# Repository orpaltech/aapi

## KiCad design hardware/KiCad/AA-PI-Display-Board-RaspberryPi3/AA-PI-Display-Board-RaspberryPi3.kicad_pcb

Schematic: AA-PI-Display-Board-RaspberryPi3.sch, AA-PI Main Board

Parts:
C1: 1u; C_0805_2012Metric_Pad1.15x1.40mm_HandSolder
C2, C9, C14, C15, C21, C26: 100n; C_0805_2012Metric_Pad1.15x1.40mm_HandSolder
C3, C7, C13: 4.7u; C_1206_3216Metric_Pad1.42x1.75mm_HandSolder
C4, C18: 10u; C_0805_2012Metric_Pad1.15x1.40mm_HandSolder
C5: 22u; C_1206_3216Metric_Pad1.42x1.75mm_HandSolder
C6: 10u; CP_EIA-3528-21_Kemet-B
C8: 47u; CP_EIA-3528-21_Kemet-B
C10, C27: 10u; C_1206_3216Metric_Pad1.42x1.75mm_HandSolder
C11, C12, C19: 10u; CP_EIA-3216-18_Kemet-A
C16, C17: 10n; C_0805_2012Metric_Pad1.15x1.40mm_HandSolder
C20: 2.2u; C_1206_3216Metric_Pad1.42x1.75mm_HandSolder
C22, C23: 22p; C_0805_2012Metric_Pad1.15x1.40mm_HandSolder
C24: 470u; CP_EIA-7343-31_Kemet-D
C25: 1u (>30V); C_1206_3216Metric_Pad1.42x1.75mm_HandSolder
D1: 1N4148; D_SOD-323_HandSoldering
D2, D3, D4, D7: B330B; D_SMB
D5: PESD5V0S1BA; D_SOD-323_HandSoldering
D6: Wall adapter; LED_0805_2012Metric_Pad1.15x1.40mm_HandSolder
D8: SS14; D_SMA
F1, F2: 2A 6V; Fuse_1206_3216Metric_Pad1.42x1.75mm_HandSolder
J1: CTP Interface; FPC-0.5-1-6P_Clamshell_Bottom
J2: USB_B_Micro; USB_Micro_B_Female_10118192
J3: USB_B_Mini; USB_Mini-B_Lumberg_2486_01_Horizontal
J4: Wall adapter; DC-050-SMD-Power-Jack
J5: MCU Power; JST_PH_B2B-PH-SM4-TB_1x02-1MP_P2.00mm_Vertical
J6: LCD Interface; FH26W-33S-0.3SHW; Manufacturer_Part_Number FH26-33S-0.3SHW
J7: Power Status; 1.25-AB-SMT-6pin-Vertical
J8: RaspberryPi MIPI-DSI Interface; FPC-1.0D-WTS-15P
J9: VNA Board Interface; 1.25-AB-SMT-10pin-Vertical
J10: MCU Interface; 1.25-AB-SMT-12pin-Vertical
J11: NTC Thermistor; JST_PH_B2B-PH-SM4-TB_1x02-1MP_P2.00mm_Vertical
J12: Battery; JST_PH_B2B-PH-SM4-TB_1x02-1MP_P2.00mm_Vertical
L1: 6.8uH; CDRH124
L2, L3: 0.5; L_0805_2012Metric_Pad1.15x1.40mm_HandSolder
L4: 10uH; CD54
Q1, Q3, Q7: IRLML6244; SOT-23
Q2, Q4, Q5, Q6, Q8: IRLML2244; SOT-23
R1, R4, R5, R9, R11, R16, R17, R20, R21, R28: 10K; R_0805_2012Metric_Pad1.15x1.40mm_HandSolder
R2, R6: 100K; R_0805_2012Metric_Pad1.15x1.40mm_HandSolder
R3: 0.5; R_0805_2012Metric_Pad1.15x1.40mm_HandSolder
R7: 300K; R_0805_2012Metric_Pad1.15x1.40mm_HandSolder
R8: 470K; R_0805_2012Metric_Pad1.15x1.40mm_HandSolder
R10: 330; R_0805_2012Metric_Pad1.15x1.40mm_HandSolder
R12, R13: 910; R_0805_2012Metric_Pad1.15x1.40mm_HandSolder
R14, R15: -; R_0805_2012Metric_Pad1.15x1.40mm_HandSolder
R18: 1.6M; R_0805_2012Metric_Pad1.15x1.40mm_HandSolder
R19: 390K; R_0805_2012Metric_Pad1.15x1.40mm_HandSolder
R22: 75K; R_0805_2012Metric_Pad1.15x1.40mm_HandSolder
R23: 2.2M; R_0805_2012Metric_Pad1.15x1.40mm_HandSolder
R24: 1K; R_0805_2012Metric_Pad1.15x1.40mm_HandSolder
R25, R26: 0; R_0805_2012Metric_Pad1.15x1.40mm_HandSolder
R27: 240K; R_0805_2012Metric_Pad1.15x1.40mm_HandSolder
R29: 33K; R_0805_2012Metric_Pad1.15x1.40mm_HandSolder
R30: 15; R_0805_2012Metric_Pad1.15x1.40mm_HandSolder
SW1: SW_SPST; SW_SPST_CK_RS282G05A3
SW2: SW_SPDT; SW_SPDT_PCM12
U1: LTC4412; SOT95P280X100-6N; Manufacturer_Part_Number LTC4412ES6#TRMPBF
U2: AMS1117-3.3; SOT-223-3_TabPin2; Manufacturer_Part_Number AMS1117-3.3
U3: WM8731; SOP65P780X200-28N; Manufacturer_Part_Number WM8731/L
U4: MCP73833; SOP50P490X110-10N; Manufacturer_Part_Number MCP73833-FCI/UN
U5: TPS61030PWP; SOP65P640X120-17N; Manufacturer_Part_Number TPS61030PWP
U6: FAN5333BSX; SOT95P270X145-5N; Manufacturer_Part_Number FAN5333BSX
Y1: 12.288M; Crystal_SMD_5032-2Pin_5.0x3.2mm

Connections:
+3V3: C8.1, C9.1, J1.1, J6.4, J6.27, J6.28, L2.1, L3.1, Q3.1, Q7.1, R4.2, R5.2, R9.2, R11.1, R16.1, R17.2, R29.2, U2.2
+5V: C6.1, C18.1, C20.1, C24.1, J5.1, J9.1, L4.1, R23.2, U2.3, U5.13, U5.14, U5.15, U6.5
/V_F2: D2.1, D3.1, D4.1, F2.1
/V_SUPPLY: C5.1, D5.2, F1.2, Q5.3
/V_USB: C3.1, F2.2, Q4.3, U1.1
/V_USB1: D2.2, J2.1
/V_USB2: D3.2, J3.1 (VBUS)
/V_WALL: F1.1, J4.1
CHRG_PG: J7.2, Q7.2, R17.1
CHRG_STAT1: J7.3, R16.2, U4.3
CHRG_STAT2: J7.4, R11.2, U4.4
CTP_INT: J1.3, J10.5
DSI_CLK_N: J6.15, J8.5
DSI_CLK_P: J6.16, J8.6
DSI_D0_N: J6.12, J8.8
DSI_D0_P: J6.13, J8.9
DSI_D1_N: J6.18, J8.2
DSI_D1_P: J6.19, J8.3
GND: C3.2, C6.2, C7.2, C8.2, C9.2, C10.2, C11.2, C12.2, C13.1, C14.2, C15.1, C16.2, C17.2, C18.2, C19.2, C20.2, C21.2, C22.2, C23.2, C24.2, C25.2, C26.2, C27.2, D4.2, D5.1, J1.6, J1.SH, J2.5, J2.SH, J3.5 (GND), J3.SH (Shield), J4.2, J4.3, J5.2, J6.1, J6.7, J6.8, J6.11, J6.14, J6.17, J6.20, J6.23, J6.26, J6.33, J6.SH1, J6.SH2, J7.6, J7.SH, J8.1, J8.4, J8.7, J8.10, J8.13, J8.SH, J9.2, J9.10, J9.SH, J10.6, J10.12, J10.SH, J11.2, J12.2, Q1.2, R3.1, R10.1, R14.1, R15.1, R19.1, R20.1, R22.2, R25.1, R27.2, R28.1, R30.2, SW1.1, U1.2, U1.3, U2.1, U3.15, U3.21, U3.22, U3.28, U4.5, U5.3, U5.4, U5.5, U5.8, U5.11, U5.17, U6.2
I2C_SCL: J1.5, J9.4, J10.2, R5.1, U3.24
I2C_SDA: J1.4, J9.3, J10.1, R4.1, U3.23
I2S_BCLK: J10.9, U3.3
I2S_DIN: J10.11, U3.6
I2S_LRCK: J10.10, U3.7
LCD_RESET: J1.2, J6.24, J10.4
LED-A: C25.1, D8.1, J6.31, J6.32
LED-K: J6.29, J6.30, R30.1, U6.3
LOW_BATT: J7.5, R29.1, U5.10
unnamed: C1.1, D1.1, R1.2, SW1.2
unnamed: C1.2, C2.2, Q1.3, Q2.1, R2.2
unnamed: C4.2, Q1.1, R7.2
unnamed: C5.2, R3.2
unnamed: C11.1, C14.1, L2.2, U3.14
unnamed: C12.1, C15.2, U3.16
unnamed: C16.1, R12.2, R14.2, U3.20
unnamed: C17.1, R13.2, R15.2, U3.19
unnamed: C19.1, C21.1, C26.1, L3.2, U3.1, U3.27
unnamed: C22.1, U3.26, Y1.2
unnamed: C23.1, U3.25, Y1.1
unnamed: C27.1, J12.1, Q8.3, U4.9, U4.10
unnamed: D1.2, Q3.3, R6.2, R7.1
unnamed: D6.1, R10.2
unnamed: D6.2, Q6.3
unnamed: D8.2, L4.2, U6.1
unnamed: J11.1, R26.2, R28.2
unnamed: L1.2, U5.1, U5.2
unnamed: Q4.1, U1.5
unnamed: Q5.1, Q6.1, R8.1, U1.4
unnamed: Q7.3, R21.2, U4.7
unnamed: R18.1, R19.2, U5.7
unnamed: R22.1, SW2.2, U6.4
unnamed: R23.1, R27.1, U5.12
unnamed: R24.1, R25.2
unnamed: R24.2, U4.6
unnamed: R26.1, U4.8
OUT_VI: J9.9, R13.1
OUT_VV: J9.8, R12.1
PWM_CABC: J6.25, SW2.1
PWM_MCU: J10.3, SW2.3
SHDN_CTRL: J7.1, Q3.2, R9.1
TE_OUT: J6.5
V_IN: C7.1, C13.2, D7.2, Q4.2, Q5.2, Q6.2, Q8.1, R8.2, R20.2, R21.1, U1.6, U4.1, U4.2
V_LOAD: C4.1, C10.1, L1.1, Q2.3, R6.1, R18.2, U5.6, U5.9
V_SW: C2.1, D7.1, Q2.2, Q8.2, R1.1, R2.1

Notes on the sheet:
The STAT pin goes low when the wall adapter is connected to the load.

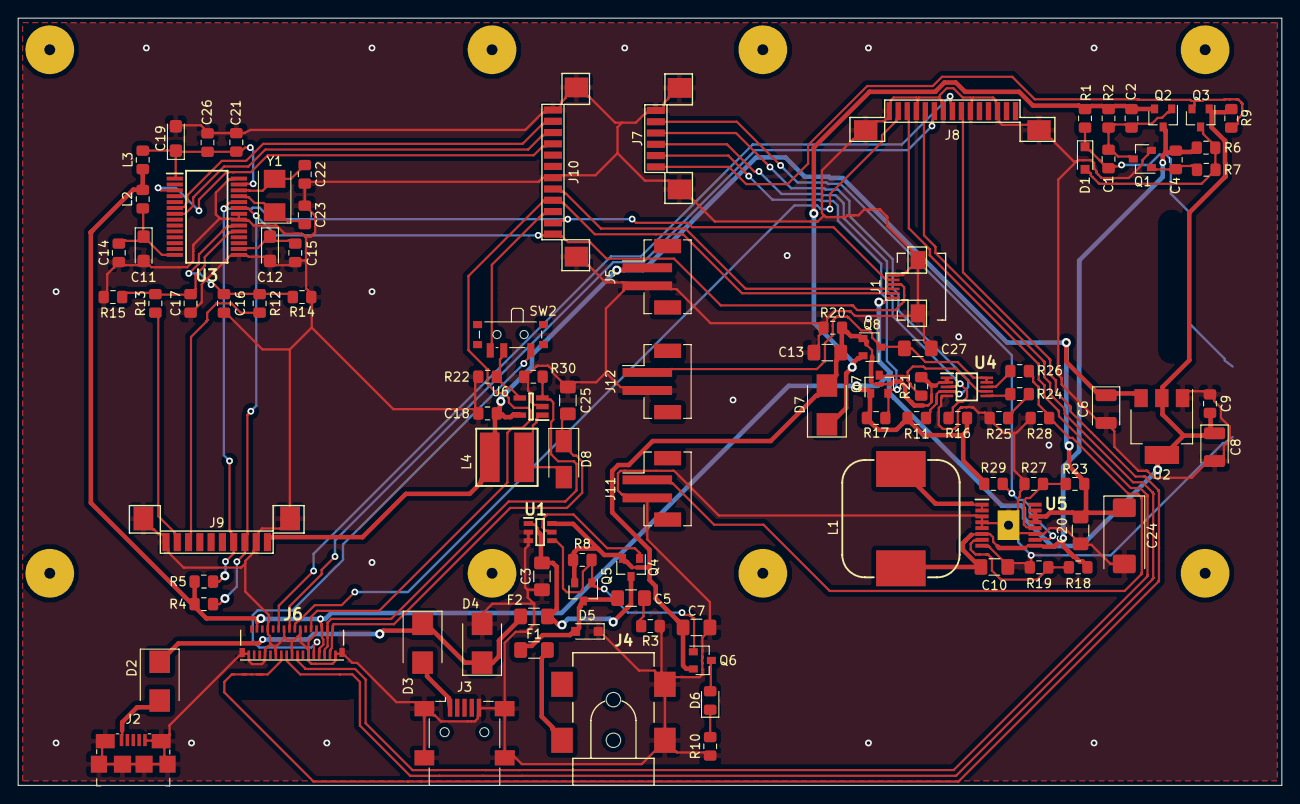
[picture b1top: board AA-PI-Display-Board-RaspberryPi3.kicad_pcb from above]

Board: 2 copper layers, 140.0 x 85.0 mm, 110 parts (1 on the bottom side), 63 nets.

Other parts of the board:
CH1: CTP-CABLE-HOLE
HOLE2: LCD-0.3-33P-CABLE-HOLE
SS1, SS2, SS3, SS4, SS5, SS6, SS7, SS8: PCB-Standoff-Spacer-SMD-M3

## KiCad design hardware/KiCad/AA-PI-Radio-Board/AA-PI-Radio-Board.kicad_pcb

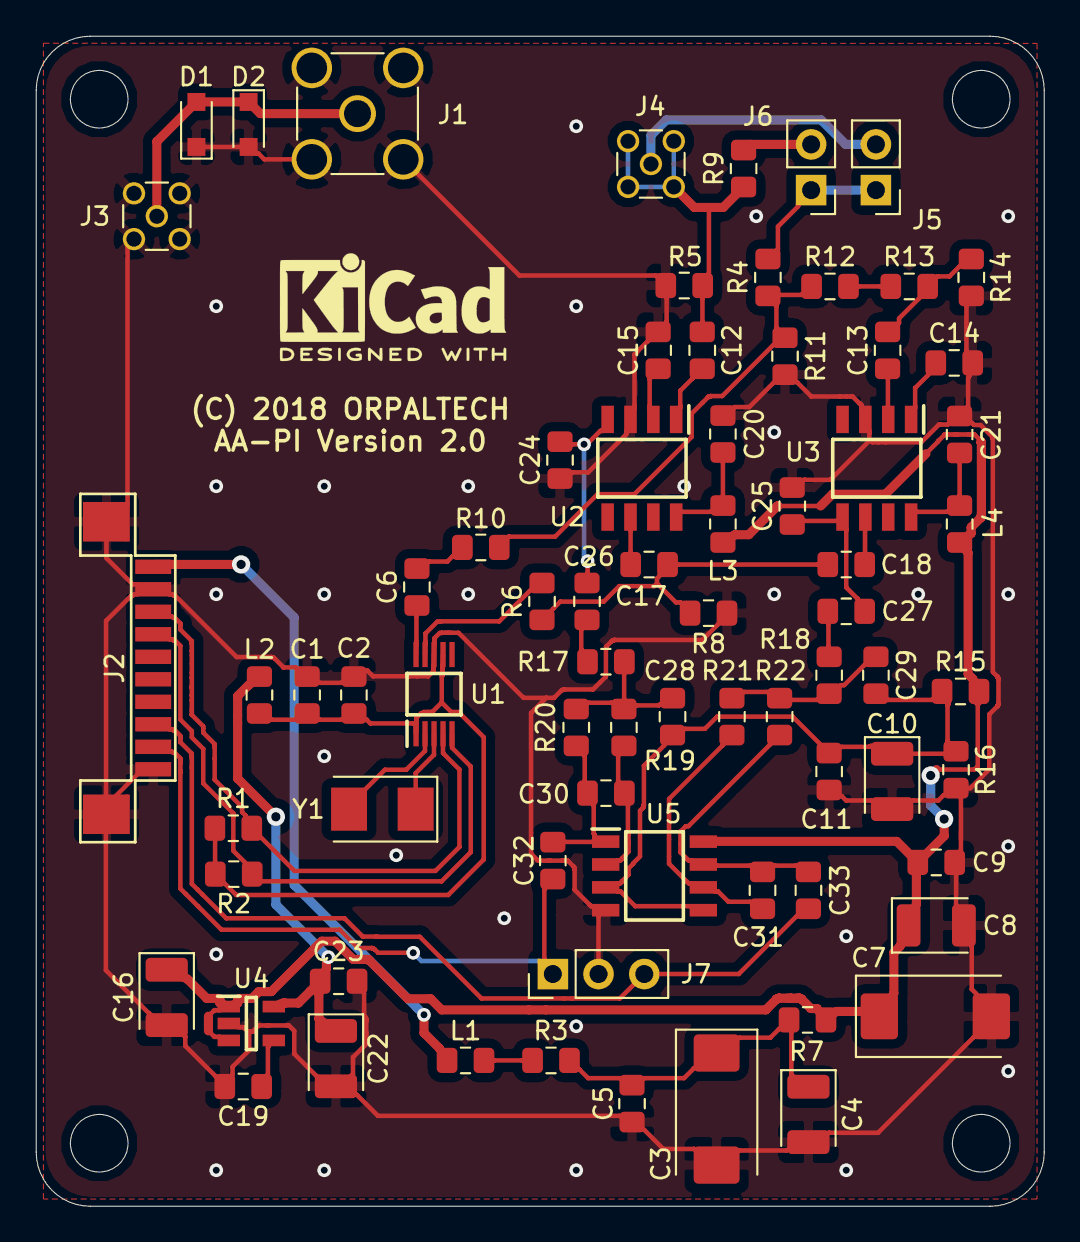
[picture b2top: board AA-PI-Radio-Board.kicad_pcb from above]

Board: 2 copper layers, 56.0 x 65.0 mm, 78 parts (0 on the bottom side), 45 nets.

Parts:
C1: 100p; C_0805_2012Metric_Pad1.15x1.40mm_HandSolder
C2, C5, C6, C9, C11, C12, C13, C14, C15, C20, C21, C23, C26, C27: 100n; C_0805_2012Metric_Pad1.15x1.40mm_HandSolder
C3, C7: 100u; CP_EIA-7343-31_Kemet-D
C4: 47u; CP_EIA-3528-21_Kemet-B
C8: 22u; CP_EIA-3528-21_Kemet-B
C10, C16, C22: 10u; CP_EIA-3528-21_Kemet-B
C17, C18: 10n; C_0805_2012Metric_Pad1.15x1.40mm_HandSolder
C19: 22n; C_0805_2012Metric_Pad1.15x1.40mm_HandSolder
C24, C25: 300p; C_0805_2012Metric_Pad1.15x1.40mm_HandSolder
C28, C29: 1n; C_0805_2012Metric_Pad1.15x1.40mm_HandSolder
C30, C31: 82p; C_0805_2012Metric_Pad1.15x1.40mm_HandSolder
C32, C33: 10u; C_0805_2012Metric_Pad1.15x1.40mm_HandSolder
D1, D2: 1N4148; D_SOD-323_HandSoldering
J1: ANT-IN; SMA_Amphenol_901-144_Vertical
J2: MAIN BOARD; 1.25-AB-SMT-10pin-Vertical
J3, J4: INDUCT; MMCX_Molex_73415-1471_Vertical
J5: WORK; PinHeader_1x02_P2.54mm_Vertical
J6: HWCAL; PinHeader_1x02_P2.54mm_Vertical
J7: V/I OUT; PinHeader_1x03_P2.54mm_Vertical
L1, L2, L3, L4: 0.5; L_0805_2012Metric_Pad1.15x1.40mm_HandSolder
MH1, MH2, MH3, MH4: MountingHole_3.2mm_M3_DIN965
R1, R2: 10K; R_0805_2012Metric_Pad1.15x1.40mm_HandSolder
R3: 12; R_0805_2012Metric_Pad1.15x1.40mm_HandSolder
R4, R12: 200; R_0805_2012Metric_Pad1.15x1.40mm_HandSolder
R5, R14: 5.1; R_0805_2012Metric_Pad1.15x1.40mm_HandSolder
R6: 1.5K; R_0805_2012Metric_Pad1.15x1.40mm_HandSolder
R7: 10; R_0805_2012Metric_Pad1.15x1.40mm_HandSolder
R8, R9, R11, R13: 51; R_0805_2012Metric_Pad1.15x1.40mm_HandSolder
R10: 510; R_0805_2012Metric_Pad1.15x1.40mm_HandSolder
R15, R16: 3.3K; R_0805_2012Metric_Pad1.15x1.40mm_HandSolder
R17, R18, R19, R21: 12K; R_0805_2012Metric_Pad1.15x1.40mm_HandSolder
R20, R22: 75K; R_0805_2012Metric_Pad1.15x1.40mm_HandSolder
U1: Si5351A; SOP50P490X110-10N
U2, U3: SA612A; SOIC127P600X175-8N
U4: RT9193-33GB; SOT94P279X130-5N
U5: MC4558; SOIC127P600X175-8N
Y1: 27M; Crystal_SMD_5032-2Pin_5.0x3.2mm

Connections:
+2V5: C10.1, C11.1, C28.2, C29.2, R15.2, R16.1, U5.3, U5.5
+3V3: C22.1, C23.1, L2.1, U4.5
+5V: C7.1, C8.1, C9.1, C16.1, L3.1, L4.1, R7.2, R15.1, U4.1, U4.3, U5.8
/V_IN: J2.1, L1.1
GND: C1.2, C2.2, C3.2, C4.2, C5.2, C7.2, C8.2, C9.2, C10.2, C11.2, C14.1, C15.2, C16.2, C19.2, C20.2, C21.2, C22.2, C23.2, C24.2, C25.2, D1.1, D2.2, J1.2, J2.2, J2.10, J2.SH, J3.2, J7.2, R5.2, R8.2, R11.1, R14.2, R16.2, U1.8, U2.3, U3.3, U4.2, U5.4
I2C_SCL: J2.3, R1.1, U1.4
I2C_SDA: J2.4, R2.1, U1.5
unnamed: C1.1, C2.1, L2.2, R1.2, R2.2, U1.1, U1.7
unnamed: C3.1, C4.1, C5.1, R3.2, R7.1
unnamed: C6.1, U1.10
unnamed: C6.2, R10.1
unnamed: C12.2, U2.1
unnamed: C13.2, U3.2
unnamed: C14.2, U3.1
unnamed: C15.1, U2.2
unnamed: C17.1, U2.6
unnamed: C17.2, C18.1, R6.2, R8.1
unnamed: C18.2, U3.6
unnamed: C19.1, U4.4
unnamed: C20.1, L3.2, U2.8
unnamed: C21.1, L4.2, U3.8
unnamed: C24.1, C26.1, U2.4
unnamed: C25.1, C27.1, U3.5
unnamed: C26.2, R17.1
unnamed: C27.2, R18.1
unnamed: C28.1, R17.2, R19.1, R20.1
unnamed: C29.1, R18.2, R21.1, R22.1
unnamed: C30.1, R19.2, U5.2
unnamed: C30.2, C32.1, R20.2, U5.1
unnamed: C31.1, R21.2, U5.6
unnamed: C31.2, C33.1, R22.2, U5.7
unnamed: D1.2, D2.1, J1.1, J3.1
unnamed: J4.1, J5.2
unnamed: J5.1, J6.1, R4.2
unnamed: J6.2, R9.1
unnamed: L1.2, R3.1
unnamed: R6.1, U1.9
unnamed: R4.1, R10.2, R11.2, R12.1
unnamed: R12.2, R13.1
unnamed: U1.2, Y1.2
unnamed: U1.3, Y1.1
OUT_VI: C32.2, J2.9, J7.1
OUT_VV: C33.2, J2.8, J7.3
VI: C12.1, J4.2, R5.1, R9.2
VV: C13.1, R13.2, R14.1

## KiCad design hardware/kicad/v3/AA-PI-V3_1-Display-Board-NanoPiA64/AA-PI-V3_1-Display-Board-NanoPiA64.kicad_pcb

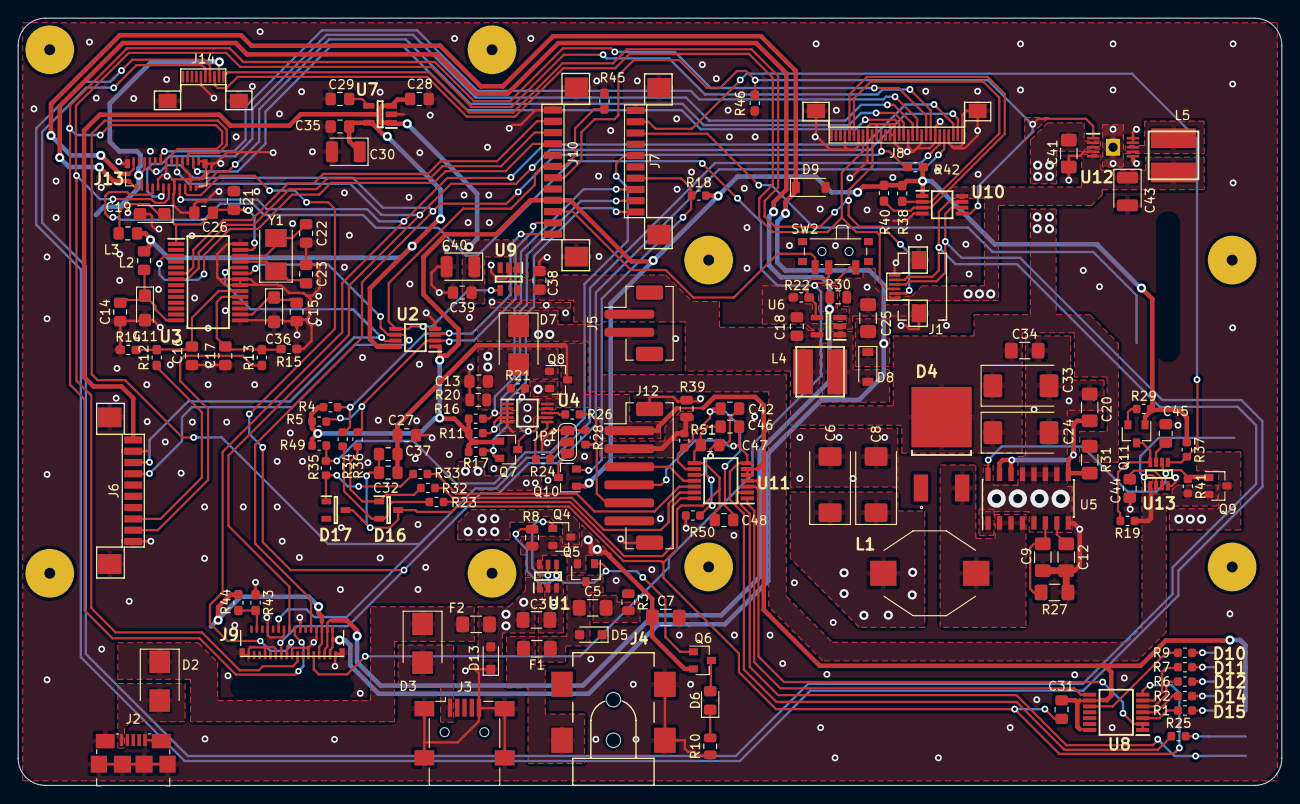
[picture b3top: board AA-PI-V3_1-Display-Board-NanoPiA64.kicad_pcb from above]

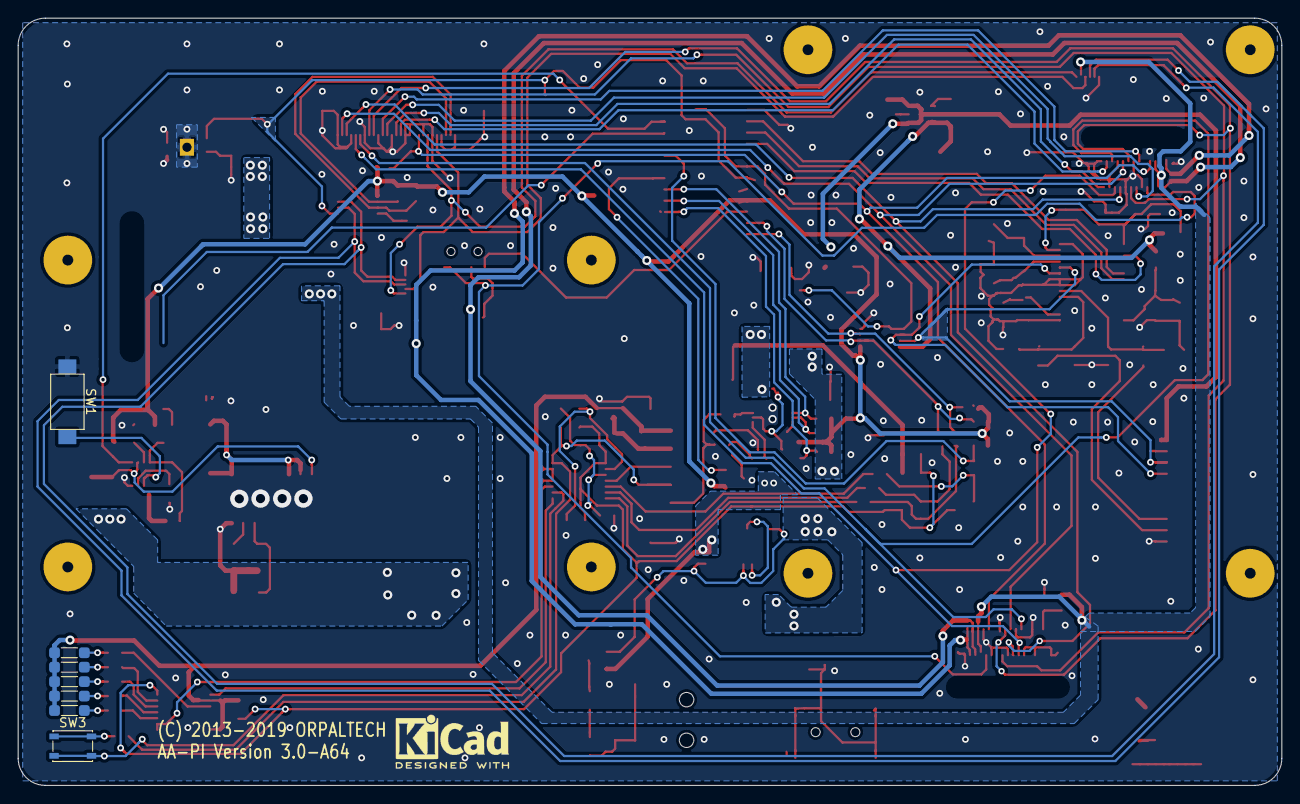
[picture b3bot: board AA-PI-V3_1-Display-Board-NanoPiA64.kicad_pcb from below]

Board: 2 copper layers, 140.0 x 85.0 mm, 165 parts (7 on the bottom side), 113 nets.

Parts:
C3, C7: 4.7u; C_1206_3216Metric_Pad1.42x1.75mm_HandSolder
C5, C41: 22u; C_1206_3216Metric_Pad1.42x1.75mm_HandSolder
C6, C8, C24, C33: 150u; CP_EIA-7343-31_Kemet-D
C9, C20, C34: 100n; C_1206_3216Metric_Pad1.42x1.75mm_HandSolder
C11, C36: 10u; CP_EIA-3216-18_Kemet-A
C12: 220n; C_1206_3216Metric_Pad1.42x1.75mm_HandSolder
C13, C18, C27: 4.7u; C_0805_2012Metric_Pad1.15x1.40mm_HandSolder
C14, C15, C21, C26, C35, C38, C39: 100n; C_0805_2012Metric_Pad1.15x1.40mm_HandSolder
C16, C17: 10n; C_0805_2012Metric_Pad1.15x1.40mm_HandSolder
C19: 22u; CP_EIA-3216-18_Kemet-A
C22, C23: 22p; C_0805_2012Metric_Pad1.15x1.40mm_HandSolder
C25: 1u; C_1206_3216Metric_Pad1.42x1.75mm_HandSolder
C28: 2.2u; C_0805_2012Metric_Pad1.15x1.40mm_HandSolder
C29: 22n; C_0805_2012Metric_Pad1.15x1.40mm_HandSolder
C30, C40, C43: 47u; CP_EIA-3528-21_Kemet-B
C31, C32, C37, C42, C47, C48: 0.1u; C_0805_2012Metric_Pad1.15x1.40mm_HandSolder
C44, C46: 1u; C_0805_2012Metric_Pad1.15x1.40mm_HandSolder
C45: 47n; C_0805_2012Metric_Pad1.15x1.40mm_HandSolder
CH1: CTP-CABLE-HOLE
D2, D3, D7: SS54; D_SMB
D4: STPS8L30B-TR; ST_DPAK
D5, D13: PESD5V0S1BA; D_SOD-323_HandSoldering
D6: Wall adapter; LED_0805_2012Metric_Pad1.15x1.40mm_HandSolder
D8: 1N5819; D_SOD-123
D9: BZT52; D_SOD-123
D10, D11, D12, D14, D15: QTLP610C-4; QTLP610C4TR_Vertical
D16, D17: AZ23C5V6; SOT96P240X110-3N
F1, F2: 3A 6V; Fuse_1206_3216Metric_Pad1.42x1.75mm_HandSolder
HOLE2: LCD-0.3-33P-CABLE-HOLE
J1: CTP Interface (6pin); FPC-0.5-1-6P_Clamshell_Bottom
J2: USB_B_Micro; USB_Micro_B_Female_10118192
J3: USB_B_Mini; USB_Mini-B_Lumberg_2486_01_Horizontal
J4: Wall adapter; DC-050-SMD-Power-Jack
J5: MCU Power; JST_PH_B2B-PH-SM4-TB_1x02-1MP_P2.00mm_Vertical
J6: VNA Board Interface; 1.25-AB-SMT-10pin-Vertical
J7: Power Control; 1.25-AB-SMT-10pin-Vertical
J8: NanoPi A64 Display Interface; FPC-0.5-1-30P_Clamshell_Bottom
J9: LCD Interface; FH26-33S-0.3SHW
J10: MCU Interface; 1.25-AB-SMT-12pin-Vertical
J12: Battery Pack; JST_PH_B6B-PH-SM4-TB_1x06-1MP_P2.00mm_Vertical
J13: LCD Interface; FH26-25S-0.3SHW
J14: CTP Interface (10pin); FPC-0.5-1-10P_Clamshell_Bottom
JP1: SolderJumper_3_Open; SolderJumper-3_P1.3mm_Open_RoundedPad1.0x1.5mm
L1: 1uH; COILCRAFT_DO3316P102MLB
L2, L3: 0.5; L_0805_2012Metric_Pad1.15x1.40mm_HandSolder
L4: 15uH; COILCRAFT_XEL5050_HandSolder
L5: 6.2uH; COILCRAFT_XEL5050_HandSolder
Q4, Q5, Q8, Q9: Si2333CDS; SOT-23
Q6: IRLML2244; SOT-23
Q7, Q10, Q11: BSS138-7-F; SOT-23
R1, R2, R6, R7, R9: 470; R_0603_1608Metric
R3: 0.5; R_0805_2012Metric
R4, R5, R21, R28, R49: 10K; R_0603_1608Metric
R8: 470K; R_0805_2012Metric
R10: 6.8K; R_0805_2012Metric
R11, R16, R17, R18, R29, R37: 33K; R_0603_1608Metric
R12, R13: 910; R_0603_1608Metric_Pad1.05x0.95mm_HandSolder
R14, R15: void; R_0603_1608Metric_Pad1.05x0.95mm_HandSolder
R19, R41: 100K; R_0603_1608Metric
R20: 10K; R_0805_2012Metric
R22, R45, R46: 100K; R_0603_1608Metric_Pad1.05x0.95mm_HandSolder
R23, R32, R33, R34, R35, R36, R50, R51: 100; R_0603_1608Metric
R24, R25: 1K; R_0603_1608Metric
R26: 0; R_0603_1608Metric
R27: 100K; R_1206_3216Metric_Pad1.42x1.75mm_HandSolder
R30: 15; R_0805_2012Metric
R31: 2; R_1206_3216Metric_Pad1.42x1.75mm_HandSolder
R38, R40, R42, R43, R44: 10K; R_0603_1608Metric_Pad1.05x0.95mm_HandSolder
R39: 0.01; R_0805_2012Metric
SS1, SS2, SS3, SS4, SS5, SS6, SS7, SS8: PCB-Standoff-Spacer-SMD-M3
SW1: ON/OFF; SW_SPST_CK_RS282G05A3
SW2: SW_SPDT; SW_SPDT_PCM12
SW3: SW_Push; SW_SPST_PTS810
U1: LTC4412; SOT95P280X100-6N
U2, U10: TCA9802; SOP65P490X110-8N
U3: WM8731; SOP65P780X200-28N
U4: MCP73833; SOP50P490X110-10N
U5: MAX1709ESE; SOIC-16_3.9x9.9mm_P1.27mm
U6: FAN5333; SOT95P270X145-5N
U7: RT9193-2HPB; SOT94P279X130-5N
U8: SN74HC164PW; SOP65P640X120-14N
U9: TPS2051BDBVR; SOT95P280X145-5N
U11: BQ34Z100PWR-G1; SOP65P640X120-14N
U12: TPS62046DGQ; SOP50P490X110-11N
U13: LTC2951-2; SOT65P280X100-8N
Y1: 12.288M; Crystal_SMD_5032-2Pin_5.0x3.2mm

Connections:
+3V3: J10.4, Q7.1, Q10.1, Q11.1, R4.2, R5.2, R11.1, R16.1, R17.2, R18.2, R29.2, R37.2, R38.2, R40.2, R42.1, R49.1, U2.1, U10.1
+5V: C18.1, C24.1, C33.1, C34.1, C38.1, C41.1, D4.1, J5.1, L4.1, R31.1, U6.5, U9.5, U12.2, U12.3
+V_ADC: C30.1, C35.1, L2.1, L3.1, U2.8, U7.5
+V_BAT: D7.1, Q8.2, Q9.2, R19.2, R41.2, U13.1
+V_IN: C7.1, C13.2, D7.2, Q4.2, Q5.2, Q6.2, Q8.1, R8.2, R20.2, R21.1, U1.6, U4.1, U4.2
+V_LCD: C43.1, J1.1, J9.27, J9.28, J13.21, J13.22, J14.9, L5.2, R44.1, U10.8, U12.5
+V_LOAD: C6.1, C8.1, L1.1, Q9.3
+V_RADIO: C28.2, C39.1, C40.1, J6.1, U7.1, U7.3, U9.1
/BAT+: C27.1, C31.1, C32.2, C37.1, D10.2, D11.2, D12.2, D14.2, D15.2, J12.1, Q8.3, U4.9, U4.10, U8.9, U8.14, U11.4, U11.5, U11.6
/BAT-: J12.2, R39.1, R51.2
/BQ_ALERT: J7.6, R35.1, R49.2
/BQ_TS1: J12.3, U11.11
/BQ_TS2: C46.1, J12.4, R25.2, U11.7
/CHRG_CTRL: J7.4, Q10.2, R18.1
/CHRG_PG: J7.1, Q7.2, R17.1
/CHRG_STAT1: J7.3, R16.2, U4.3
/CHRG_STAT2: J7.2, R11.2, U4.4
/CHRG_TS: J12.5, R26.1, R28.2
/MAX1709_LX: D4.2, L1.2, U5.2, U5.3, U5.4
/MAX1709_OUT: C20.1, R31.2, U5.9, U5.14, U5.15
/MAX1709_REF: C12.1, U5.7
/MAX1709_SSLIM: C9.1, R27.1, U5.6
/SHDN_CTRL: J7.8, Q11.2, R29.1
/SHDN_REQ: J7.9, R37.1, U13.5
/V_F2: D2.1, D3.1, F2.1
/V_SUPPLY: C5.1, D5.2, F1.2, Q5.3
/V_USB: C3.1, D13.2, F2.2, Q4.3, U1.1
/V_USB1: D2.2, J2.1
/V_USB2: D3.2, J3.1
/V_WALL: F1.1, J4.1
BAT_GND: C31.2, C32.1, C37.2, C46.2, C47.2, C48.2, D16.3, D17.3, U8.7, U11.8
CTP_INT: J1.3, J8.23, J14.8
CTP_RESET: J1.2, J8.21, J14.10
DSI_CLK_N: J8.3, J9.15, J13.8
DSI_CLK_P: J8.2, J9.16, J13.9
DSI_D0_N: J8.6, J9.12, J13.5
DSI_D0_P: J8.5, J9.13, J13.6
DSI_D1_N: J8.9, J9.18, J13.11
DSI_D1_P: J8.8, J9.19, J13.12
DSI_D2_N: J8.12, J13.14
DSI_D2_P: J8.11, J13.15
DSI_D3_N: J8.14, J13.2
DSI_D3_P: J8.15, J13.3
GND: C3.2, C6.2, C7.2, C8.2, C9.2, C11.2, C12.2, C13.1, C14.2, C15.1, C16.2, C17.2, C18.2, C19.2, C20.2, C21.2, C22.2, C23.2, C24.2, C25.2, C26.2, C27.2, C28.1, C29.2, C30.2, C33.2, C34.2, C35.2, C36.2, C38.2, C39.2, C40.2, C41.2, C43.2, C44.2, C45.2, D5.1, D9.2, D13.1, J1.6, J1.SH, J2.5, J2.SH, J3.5, J3.SH, J4.2, J4.3, J5.2, J6.2, J6.10, J6.SH, J7.10, J7.SH, J8.1, J8.4, J8.7, J8.10, J8.13, J8.16, J8.17, J8.20, J8.22, J8.24, J8.27, J8.SH, J9.1, J9.7, J9.8, J9.11, J9.14, J9.17, J9.20, J9.23, J9.26, J9.33, J9.SH1, J9.SH2, J10.12, J10.SH, J12.6, J12.SH, J13.1, J13.4, J13.7, J13.10, J13.13, J13.16, J13.SH1, J13.SH2, J14.5, J14.SH, JP1.1, R3.1, R10.1, R14.1, R15.1, R20.1, R22.2, R27.2, R28.1, R30.2, R39.2, R43.1, R45.1, R46.2, R50.2, SW1.1, U1.2, U1.3, U2.4, U3.15, U3.21, U3.22, U3.28, U4.5, U5.1, U5.5, U5.8, U5.10, U5.11, U5.12, U5.13, U6.2, U7.2, U9.2, U10.4, U12.4, U12.6, U12.9, U12.10, U12.11, U13.4
I2C0_SCL: J8.25, R38.1, U10.2
I2C0_SDA: J8.26, R40.1, U10.3
I2C_SCL: J10.2, R5.1, R36.1, U2.2
I2C_SDA: J10.1, R4.1, R34.1, U2.3
I2S_BCLK: J10.9, U3.3
I2S_DIN: J10.11, U3.6
I2S_LRCK: J10.10, U3.7
LCD_RESET: J8.19, J9.24, J13.19, R42.2
LCM_ID: J9.4, R43.2, R44.2
LED-A: C25.1, D8.1, D9.1, J9.31, J9.32, J13.25
LED-K: J9.29, J9.30, J13.24, R30.1, U6.3
unnamed: C5.2, R3.2
unnamed: C11.1, C14.1, L2.2, U3.14
unnamed: C15.2, C36.1, U3.16
unnamed: C16.1, R12.2, R14.2, U3.20
unnamed: C17.1, R13.2, R15.2, U3.19
unnamed: C19.1, C21.1, C26.1, L3.2, U3.1, U3.27
unnamed: C22.1, U3.26, Y1.2
unnamed: C23.1, U3.25, Y1.1
unnamed: C29.1, U7.4
unnamed: C42.1, C48.1, R51.1, U11.9
unnamed: C42.2, C47.1, R50.1, U11.10
unnamed: C44.1, U13.3
unnamed: C45.1, U13.7
unnamed: D6.1, R10.2
unnamed: D6.2, Q6.3
unnamed: D8.2, L4.2, U6.1
unnamed: D10.1, R9.2
unnamed: D11.1, R7.2
unnamed: D12.1, R6.2
unnamed: D14.1, R2.2
unnamed: D15.1, R1.2
unnamed: D16.1, R32.1, R36.2
unnamed: D16.2, R23.1, R34.2
unnamed: D17.1, R33.1, R35.2
unnamed: JP1.2, R24.1
unnamed: JP1.3, Q10.3
unnamed: L5.1, U12.7, U12.8
unnamed: Q4.1, U1.5
unnamed: Q5.1, Q6.1, R8.1, U1.4
unnamed: Q7.3, R21.2, U4.7
unnamed: Q9.1, R41.1, U5.16, U13.6
unnamed: Q11.3, R19.1, U13.8
unnamed: R1.1, U8.3
unnamed: R2.1, U8.4
unnamed: R6.1, U8.5
unnamed: R7.1, U8.6
unnamed: R9.1, U8.10
unnamed: R22.1, SW2.2, U6.4
unnamed: R23.2, U11.14
unnamed: R24.2, U4.6
unnamed: R25.1, SW3.1
unnamed: R26.2, U4.8
unnamed: R32.2, U11.13
unnamed: R33.2, U11.12
unnamed: SW1.2, U13.2
unnamed: SW3.2, U11.2
unnamed: U8.8, U11.1
unnamed: U8.1, U8.2, U11.3
PANEL_EN: J10.6, R46.1, U10.5, U12.1
PANEL_I2C_SCL: J1.5, J14.6, U10.7
PANEL_I2C_SDA: J1.4, J14.7, U10.6
PWM_CABC: J9.25, J13.18, SW2.1
PWM_MCU: J10.3, SW2.3
RADIO_EN: J10.7, R45.2, U2.5, U9.4
VNA_I2C_SCL: J6.3, U2.7, U3.24
VNA_I2C_SDA: J6.4, U2.6, U3.23
VNA_OUT_VI: J6.9, R13.1
VNA_OUT_VV: J6.8, R12.1

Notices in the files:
hardware/KiCad/AA-PI-Radio-Board/AA-PI-Radio-Board.kicad_pcb:
(C) 2018 ORPALTECH
hardware/kicad/v3/AA-PI-V3_1-Display-Board-NanoPiA64/AA-PI-V3_1-Display-Board-NanoPiA64.kicad_pcb:
(C) 2013-2019 ORPALTECH
